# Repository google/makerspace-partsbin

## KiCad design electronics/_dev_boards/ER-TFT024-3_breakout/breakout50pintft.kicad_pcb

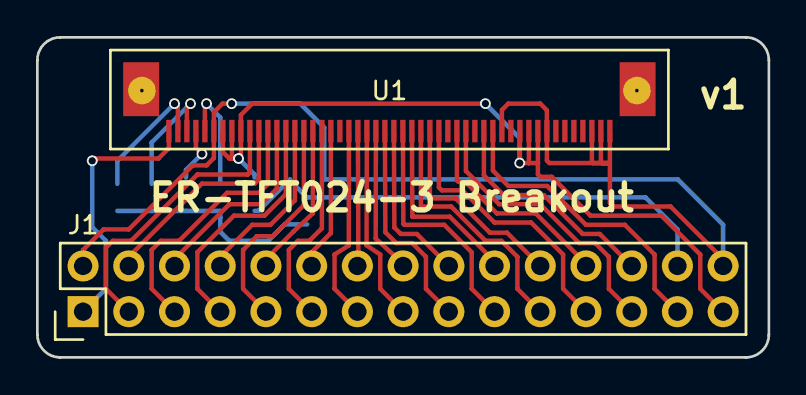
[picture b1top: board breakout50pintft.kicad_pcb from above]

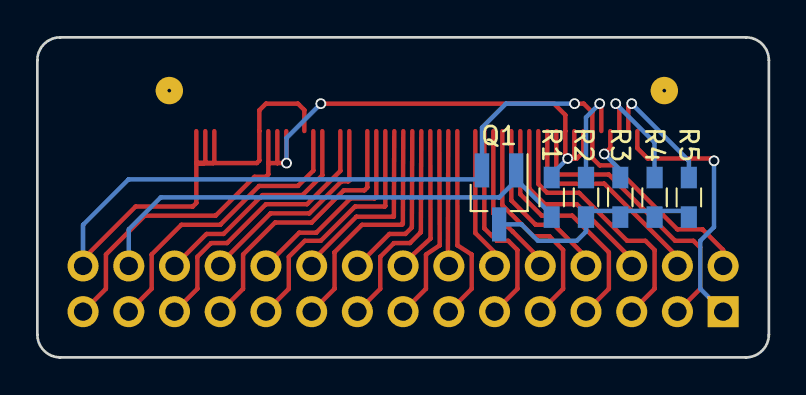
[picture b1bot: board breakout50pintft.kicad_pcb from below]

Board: 2 copper layers, 40.6 x 17.8 mm, 8 parts (6 on the bottom side), 34 nets.

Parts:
J1: CONN_02X15; Pin_Header_Straight_2x15
Q1: Q_PMOS_GSD; SOT-23_Handsoldering
R1: 10k; R_0603_HandSoldering
R2, R3, R4, R5: 330; R_0603_HandSoldering
U1: ER-TFT024-3; ZIF_50

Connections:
+3V3: J1.29, R1.2, U1.7, U1.8, U1.9, U1.40, U1.41, U1.42
+5V: J1.1, U1.1
BL: J1.28, Q1.1, R1.1
BLU3: J1.23, U1.31
BLU4: J1.22, U1.30
BLU5: J1.21, U1.29
BLU6: J1.20, U1.28
BLU7: J1.19, U1.27
CLOCK: J1.6, U1.13
DC: J1.26, U1.36
DEN: J1.7, U1.14
GND: J1.2, J1.30, Q1.2, U1.6, U1.38, U1.43, U1.48, U1.49, U1.50
GRE2: J1.18, U1.26
GRE3: J1.17, U1.25
GRE4: J1.16, U1.24
GRE5: J1.15, U1.23
GRE6: J1.14, U1.22
GRE7: J1.13, U1.21
HSYNC: J1.5, U1.12
MISO: J1.24, U1.33
MOSI: J1.25, U1.34
unnamed: Q1.3, R2.1, R3.1, R4.1, R5.1
unnamed: R2.2, U1.5
unnamed: R3.2, U1.4
unnamed: R4.2, U1.3
unnamed: R5.2, U1.2
RED3: J1.12, U1.19
RED4: J1.11, U1.18
RED5: J1.10, U1.17
RED6: J1.9, U1.16
RED7: J1.8, U1.15
RST: J1.3, U1.10
SCL: J1.27, U1.37
VSYNC: J1.4, U1.11

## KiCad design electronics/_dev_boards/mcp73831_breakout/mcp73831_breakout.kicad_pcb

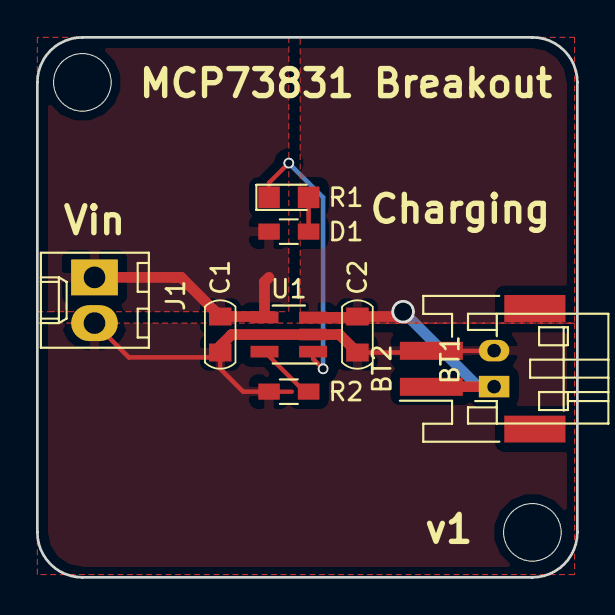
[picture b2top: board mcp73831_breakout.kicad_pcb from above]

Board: 2 copper layers, 30.0 x 30.0 mm, 10 parts (0 on the bottom side), 6 nets.

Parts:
BT1: Battery_Cell; JST_PH_S2B-PH-K_02x2.00mm_Angled
BT2: Battery_Cell; JST_PH_S2B-PH-SM4-TB_02x2.00mm_Angled
C1, C2: 4.7u; C_0805
D1: LED; LED_0805
J1: CONN_01X02; Molex_KK-6410-02_02x2.54mm_Straight
P1: SYMBOL; Board_Outline_30mm_Square
R1: 1k; R_0603_HandSoldering
R2: 2k; R_0603_HandSoldering
U1: MCP73831; SOT-23-5_HandSoldering

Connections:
/Vbat: BT1.1, BT2.1, C2.1, U1.3
/Vin: C1.1, J1.1, R1.2, U1.4
GND: BT1.2, BT2.2, C1.2, C2.2, J1.2, R2.2, U1.2
unnamed: D1.1, U1.1
unnamed: D1.2, R1.1
unnamed: R2.1, U1.5

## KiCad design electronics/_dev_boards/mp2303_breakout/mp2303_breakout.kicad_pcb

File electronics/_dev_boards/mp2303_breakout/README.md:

Not just for the 2303, also fits various newer MP devices such as MP2365.

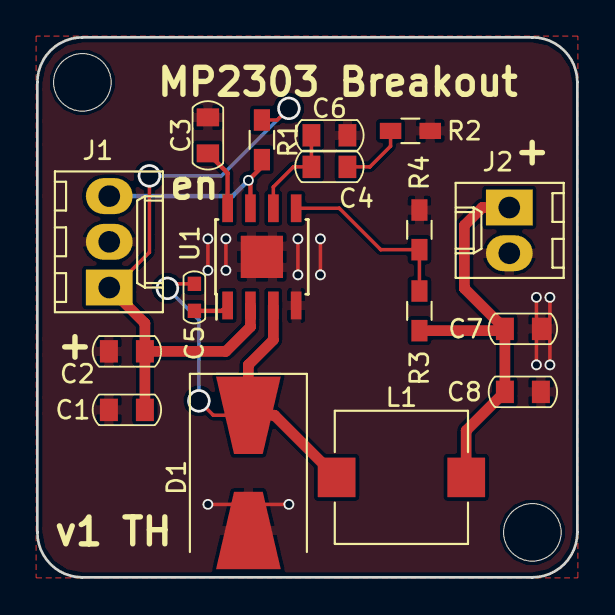
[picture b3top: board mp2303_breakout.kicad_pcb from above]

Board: 2 copper layers, 30.0 x 30.0 mm, 18 parts (0 on the bottom side), 10 nets.

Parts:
C1, C2: 10u; C_0805
C3: 0.1u; C_0805
C4: 3.3n; C_0805
C5: C; C_0603
C6: 50p; C_0805
C7, C8: 22u; C_0805
D1: D_Schottky; D_SMB-SMC_Universal_Handsoldering
J1: CONN_01X03; Molex_KK-6410-03_03x2.54mm_Straight
J2: CONN_01X02; Molex_KK-6410-02_02x2.54mm_Straight
L1: L; L_7.3x7.3_Handsoldering
P1: SYMBOL; Outline_30
R1, R2: 100k; R_0603_HandSoldering
R3: 52.5k; R_0603_HandSoldering
R4: 10k; R_0603_HandSoldering
U1: MP2303; SOIC-8-1EP_3.9x4.9mm_Pitch1.27mm

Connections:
/Vin: C1.1, C2.1, J1.1, R1.1, U1.2
/Vout: C7.1, C8.1, J2.1, L1.2, R3.1
/Vsw: C5.2, D1.1, L1.1, U1.3
GND: C1.2, C2.2, C3.2, C6.2, C7.2, C8.2, D1.2, J1.2, J2.2, R2.2, R4.2, U1.4, U1.9
unnamed: C3.1, U1.8
unnamed: C4.1, C6.1, U1.6
unnamed: C4.2, R2.1
unnamed: C5.1, U1.1
unnamed: J1.3, R1.2, U1.7
unnamed: R3.2, R4.1, U1.5

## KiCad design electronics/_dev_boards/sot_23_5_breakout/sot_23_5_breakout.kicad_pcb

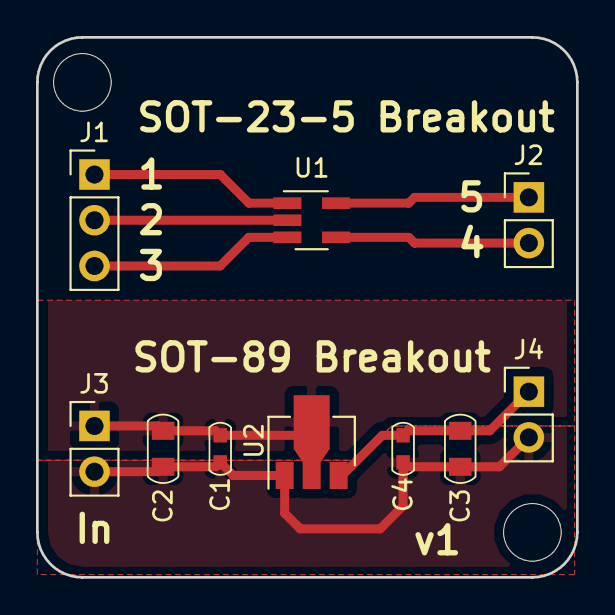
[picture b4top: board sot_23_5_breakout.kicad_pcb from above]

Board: 2 copper layers, 30.0 x 30.0 mm, 11 parts (0 on the bottom side), 8 nets.

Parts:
C1, C4: C; C_0603
C2, C3: C; C_0805
J1: CONN_01X03; Pin_Header_Straight_1x03_Pitch2.54mm
J2, J3, J4: CONN_01X02; Pin_Header_Straight_1x02_Pitch2.54mm
P1: SYMBOL; Board_Outline_30mm_Square
U1: SOT-23-5; SOT-23-5_HandSoldering
U2: MCP1703A-3302/MB; SOT89-3_Housing

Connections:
unnamed: C1.1, C2.1, J3.1, U2.2
unnamed: C1.2, C2.2, C3.2, C4.2, J3.2, J4.2, U2.1
unnamed: C3.1, C4.1, J4.1, U2.3
unnamed: J1.1, U1.1
unnamed: J1.2, U1.2
unnamed: J1.3, U1.3
unnamed: J2.1, U1.5
unnamed: J2.2, U1.4

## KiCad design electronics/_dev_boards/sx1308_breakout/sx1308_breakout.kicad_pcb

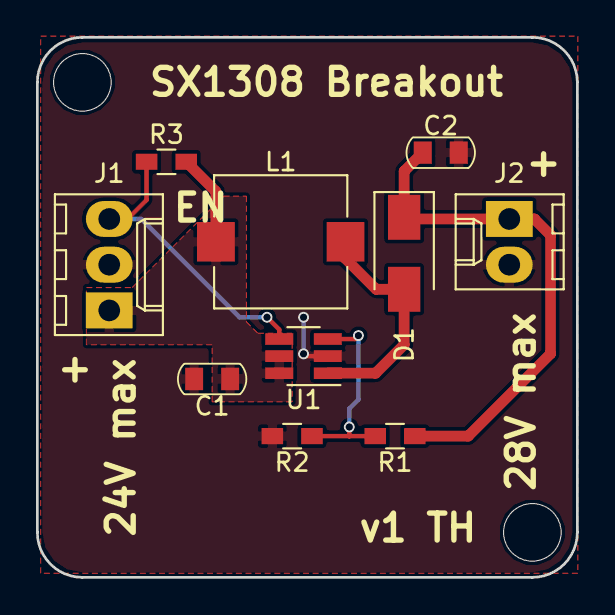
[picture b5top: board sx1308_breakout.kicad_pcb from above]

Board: 2 copper layers, 30.0 x 30.0 mm, 11 parts (0 on the bottom side), 6 nets.

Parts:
C1, C2: 22u; C_0805
D1: D_Schottky; D_SMA
J1: CONN_01X03; Molex_KK-6410-03_03x2.54mm_Straight
J2: CONN_01X02; Molex_KK-6410-02_02x2.54mm_Straight
L1: L; L_7.3x7.3_Handsoldering
P1: SYMBOL; Outline_30
R1, R2: R; R_0603_HandSoldering
R3: 100k; R_0603_HandSoldering
U1: SX1308; SOT-23-6_Handsoldering

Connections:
/Vin: C1.1, J1.1, L1.1, R3.1, U1.5, U1.6
/Vout: C2.1, D1.1, J2.1, R1.1
/Vsw: D1.2, L1.2, U1.1
GND: C1.2, C2.2, J1.2, J2.2, R2.2, U1.2
unnamed: J1.3, R3.2, U1.4
unnamed: R1.2, R2.1, U1.3

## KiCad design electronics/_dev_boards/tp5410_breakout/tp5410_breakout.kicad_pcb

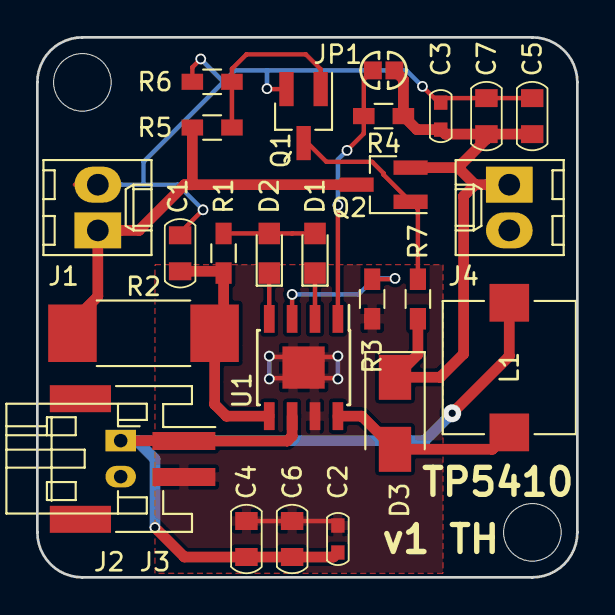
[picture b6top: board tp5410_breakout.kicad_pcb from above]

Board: 2 copper layers, 30.0 x 30.0 mm, 27 parts (0 on the bottom side), 13 nets.

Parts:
C1: 10u; C_0805
C2, C3: 0.1u; C_0603
C4, C5, C6, C7: 22u; C_0805
D1, D2: LED; LED_0805
D3: D; D_SMA
J1, J4: CONN_01X02; Molex_KK-6410-02_02x2.54mm_Straight
J2: CONN_01X02; JST_PH_S2B-PH-K_02x2.00mm_Angled
J3: CONN_01X02; JST_PH_S2B-PH-SM4-TB_02x2.00mm_Angled
JP1: Jumper_NO_Small; SJ_1_NO
L1: 4.7uH; L_7.3x7.3_Handsoldering
P1: 30mm; Outline_30
Q1: MMBT3904; SOT-23_Handsoldering
Q2: AO3401; SOT-23_Handsoldering
R1: R; R_0603_HandSoldering
R2: 0R3; R_2512_HandSoldering
R3: 680; R_0603_HandSoldering
R4: 293k; R_0603_HandSoldering
R5, R6: 5k; R_0603_HandSoldering
R7: 10k; R_0603_HandSoldering
U1: TP5410; SOIC-8-1EP_3.9x4.9mm_Pitch1.27mm

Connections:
/Vbat: C2.1, C4.1, C6.1, J2.1, J3.1, L1.2, U1.6
/Vchg: C1.1, R1.1, R2.2, U1.5
/Vin: J1.1, Q2.3, R2.1, R5.1
/Vout: C3.1, C5.1, C7.1, D3.1, J4.1, JP1.2, Q2.2, R4.2, R7.1
/Vsw: D3.2, L1.1, U1.8
GND: C1.2, C2.2, C3.2, C4.2, C5.2, C6.2, C7.2, J1.2, J2.2, J3.2, J4.2, Q1.2, R3.2, R6.2, U1.7, U1.9
unnamed: D1.1, U1.2
unnamed: D1.2, D2.2, R1.2
unnamed: D2.1, U1.4
unnamed: JP1.1, R4.1, U1.1
unnamed: Q1.1, R5.2, R6.1
unnamed: Q1.3, Q2.1, R7.2
unnamed: R3.1, U1.3

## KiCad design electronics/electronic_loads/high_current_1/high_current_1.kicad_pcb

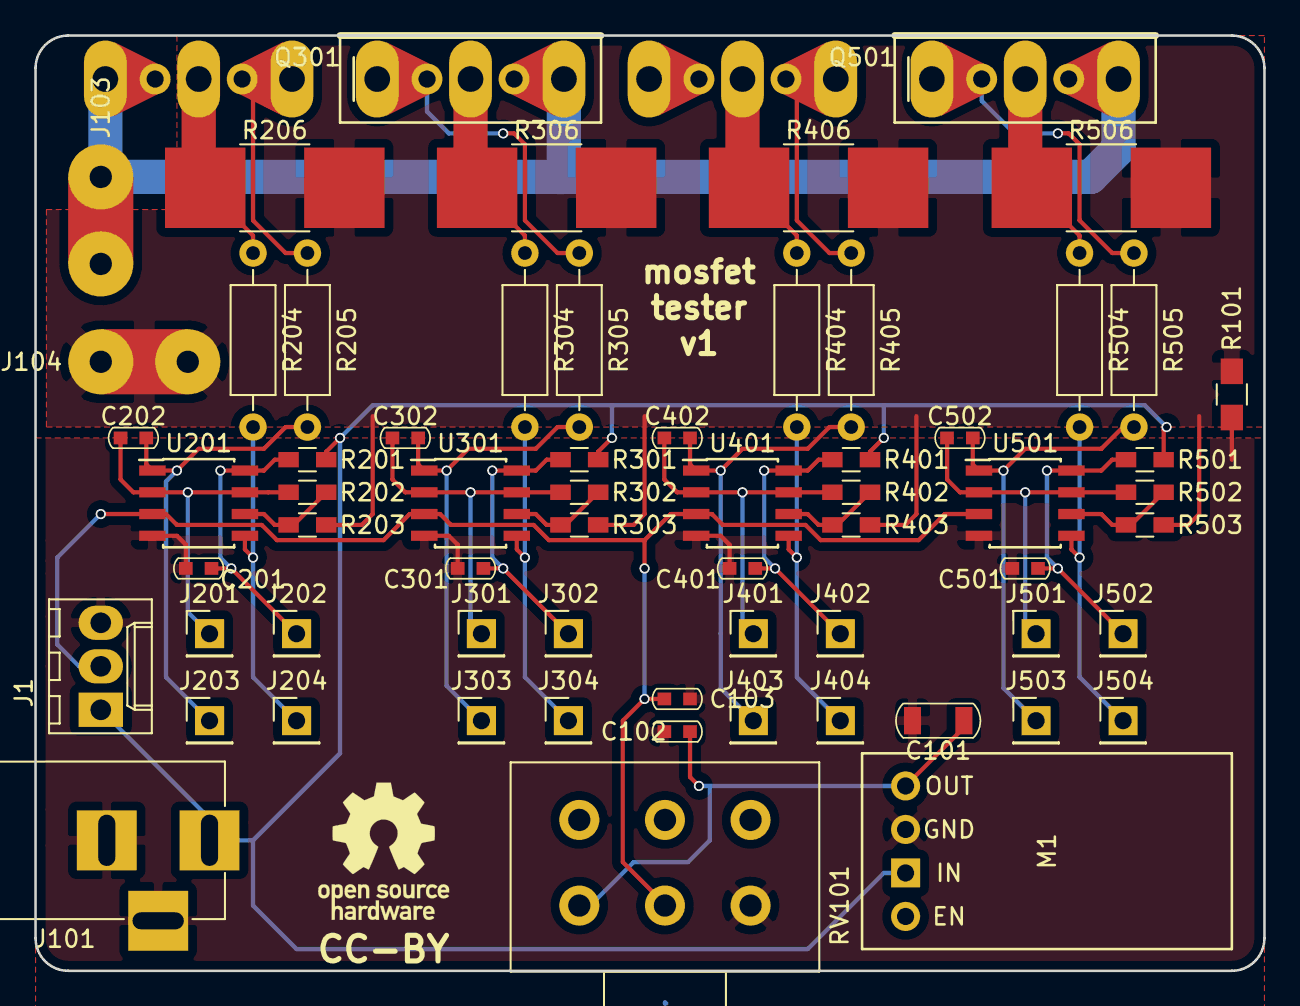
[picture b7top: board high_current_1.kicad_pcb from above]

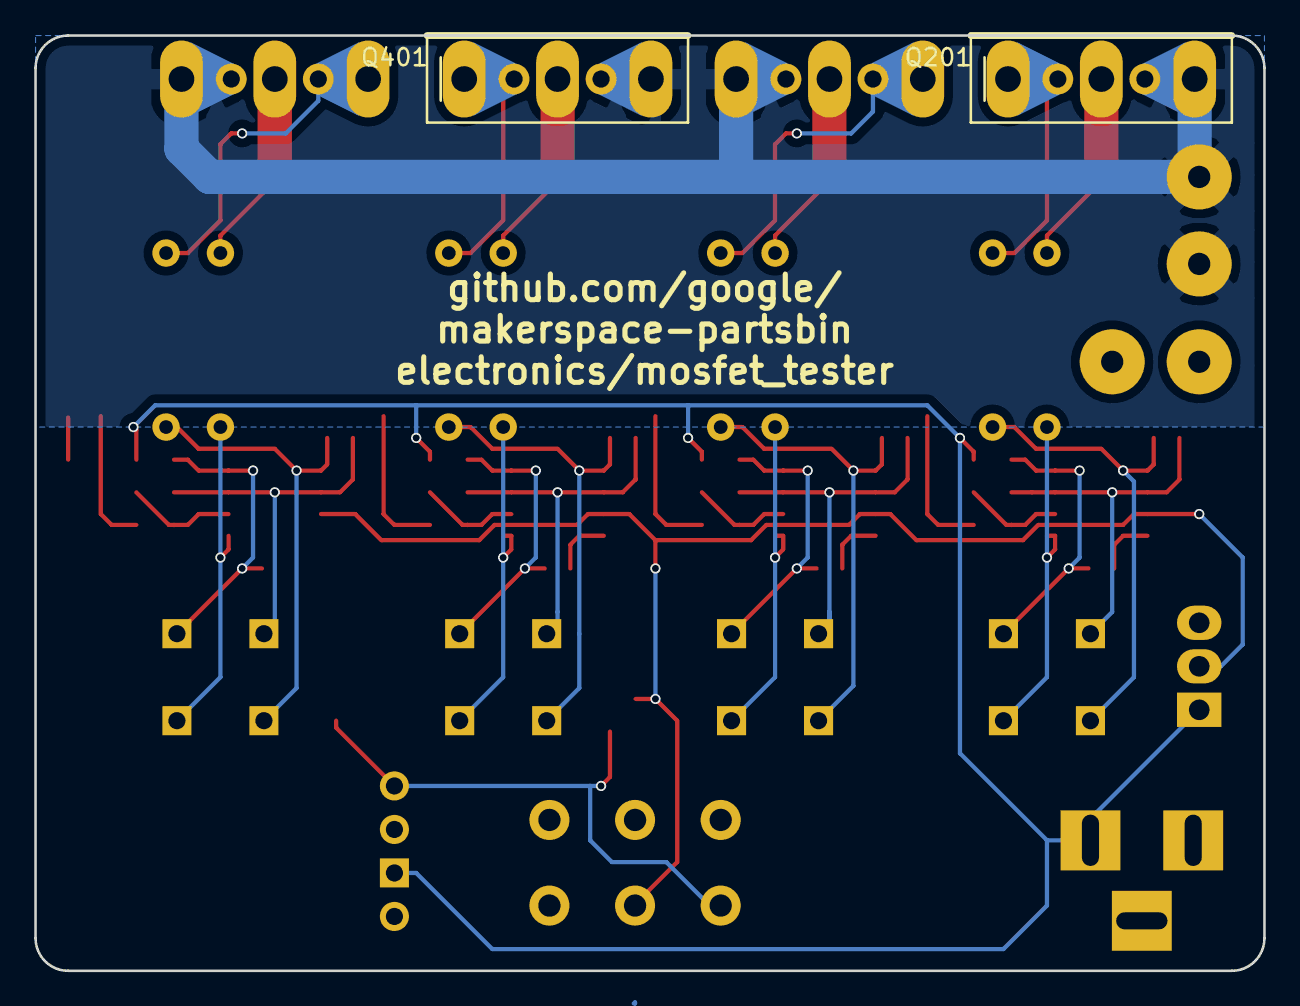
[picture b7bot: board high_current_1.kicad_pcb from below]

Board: 2 copper layers, 71.8 x 54.6 mm, 67 parts (2 on the bottom side), 34 nets.

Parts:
C101: 22u; C_1206
C102: 0.1u; C_0603
C103, C201, C301, C401, C501: 0.1; C_0603
C202, C302, C402, C502: C; C_0603
J1: CONN_01X03; Molex_KK-6410-03_03x2.54mm_Straight
J101: BARREL_JACK
J103, J104: Screw_Terminal_1x01; 2_Pin_Quick_Fit
J201, J202, J203, J204, J301, J302, J303, J304, J401, J402, J403, J404, J501, J502, J503, J504: TEST_1P; Pin_Header_Straight_1x01_Pitch2.54mm
M1: BuckModule; Buck_Module_7805_Replacement_Universal
P101: OSHW; OSHW-Logo_7.5x8mm_SilkScreen
Q201, Q301, Q401, Q501: Q_NMOS_GSD; TO_220_247
R101: 0R; R_0805_HandSoldering
R201, R301, R401, R501: 100R; R_0603_HandSoldering
R202, R203, R302, R303, R402, R403, R502, R503: R; R_0603_HandSoldering
R204, R205, R304, R305, R404, R405, R504, R505: R; R_Axial_DIN0207_L6.3mm_D2.5mm_P10.16mm_Horizontal
R206, R306, R406, R506: R; R_2816_HandSoldering
RV101: 10K; Potentiometer_Alps_RK163_Double_Vertical
U201, U301, U401, U501: LM358; SOIC-8_3.9x4.9mm_Pitch1.27mm

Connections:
+5V: C101.1, C102.1, M1.3, RV101.1
+12V: J1.1, J101.1, M1.1, R201.1, R301.1, R401.1, R501.1
/slice1/5V_REF: C103.1, J1.2, RV101.2, U201.3, U301.3, U401.3, U501.3
/slice1/VIN+: J103.1, Q201.3, Q301.3, Q401.3, Q501.3
/slice1/VIN-: J104.1, R101.1, R203.1, R206.2, R303.1, R306.2, R403.1, R406.2, R503.1, R506.2
/slice1/Vgs: C202.1, J203.1, R205.2, U201.1
/slice2/Vgs: C302.1, J303.1, R305.2, U301.1
/slice3/Vgs: C402.1, J403.1, R405.2, U401.1
/slice4/Vgs: C502.1, J503.1, R505.2, U501.1
GND: C101.2, C102.2, C103.2, C201.1, C301.1, C401.1, C501.1, J1.3, J101.2, J101.3, M1.2, R101.2, RV101.3, U201.4, U301.4, U401.4, U501.4
unnamed: C201.2, J202.1, R201.2, U201.8
unnamed: C202.2, J201.1, R202.2, U201.2, U201.7
unnamed: C301.2, J302.1, R301.2, U301.8
unnamed: C302.2, J301.1, R302.2, U301.2, U301.7
unnamed: C401.2, J402.1, R401.2, U401.8
unnamed: C402.2, J401.1, R402.2, U401.2, U401.7
unnamed: C501.2, J502.1, R501.2, U501.8
unnamed: C502.2, J501.1, R502.2, U501.2, U501.7
unnamed: J204.1, R204.2, U201.5
unnamed: J304.1, R304.2, U301.5
unnamed: J404.1, R404.2, U401.5
unnamed: J504.1, R504.2, U501.5
unnamed: Q201.1, R205.1
unnamed: Q201.2, R204.1, R206.1
unnamed: Q301.1, R305.1
unnamed: Q301.2, R304.1, R306.1
unnamed: Q401.1, R405.1
unnamed: Q401.2, R404.1, R406.1
unnamed: Q501.1, R505.1
unnamed: Q501.2, R504.1, R506.1
unnamed: R202.1, R203.2, U201.6
unnamed: R302.1, R303.2, U301.6
unnamed: R402.1, R403.2, U401.6
unnamed: R502.1, R503.2, U501.6

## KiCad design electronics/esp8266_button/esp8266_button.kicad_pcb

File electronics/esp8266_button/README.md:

# Basic use

Assemble board.  The board itself is 40x50mm, and the mounting holes (centered)
are 32x42mm.  You probably want a 3d printed housing for it, but you need to
choose whether it's powered all the time (using deep sleep), or fully powers off
unless you tap SW1.  (Close one of "DSleep" or "Button" solder jumpers.)

Keep GPIO12 set HIGH to power things (including the battery monitor ADC pin and
the BMP180 header), otherwise set LOW to conserve power.

Shields based on the Wemos D1 Mini pinout should fit (though collide with SW1),
and will also be depowered by GPIO12.

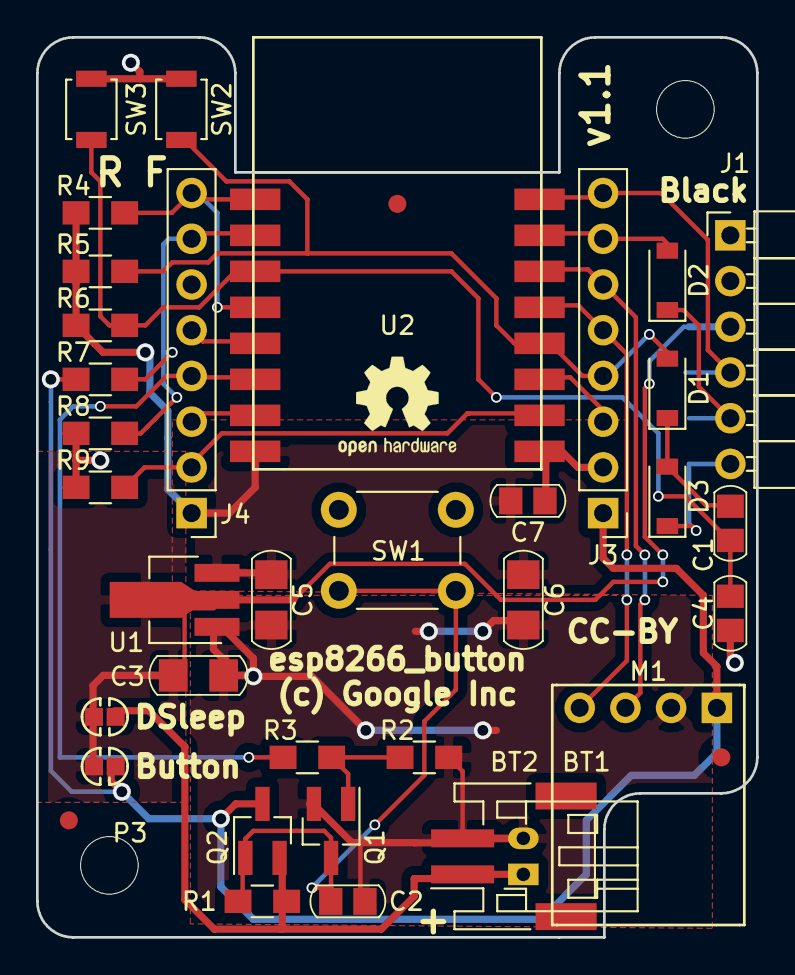
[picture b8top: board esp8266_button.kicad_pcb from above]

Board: 2 copper layers, 40.0 x 50.0 mm, 41 parts (1 on the bottom side), 23 nets.

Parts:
BT1: Battery_Cell; JST_PH_S2B-PH-K_02x2.00mm_Angled
BT2: Battery_Cell; JST_PH_S2B-PH-SM4-TB_02x2.00mm_Angled
C1, C2, C4, C7: 220p; C_0805
C3, C5, C6: 10u; C_1206
D1, D2, D3: B5819W; D_SOD-123
J1: CONN_01X06; Pin_Header_Angled_1x06_Pitch2.54mm
J2: CONN_01X06; Pogo_6
J3, J4: CONN_01X08; Pin_Header_Straight_1x08_Pitch2.54mm
JP1: Always On; SJ_1_NO
JP2: MOS Control; SJ_1_NO
M1: BMP180_Breakout; BMxx80
P1, P2, P3: Fid; Fiducial_1mm_Dia_2.54mm_Outer_CopperTop
P4: OSHW; OSHW-Logo2_7.3x6mm_SilkScreen
P5, P6: M3 Hole; MountingHole_3.2mm_M3
Q1: Q_NMOS_GSD; SOT-23_Handsoldering
Q2: Q_PMOS_GSD; SOT-23_Handsoldering
R1, R8: 100k; R_0805_HandSoldering
R2: 220k; R_0805_HandSoldering
R3, R4, R5, R6, R9: 10k; R_0805_HandSoldering
R7: 320k; R_0805_HandSoldering
SW1: SW_Push; SW_PUSH_6mm
SW2, SW3: SW_Push; SW_SPST_B3U-1000P
U1: MCP1703A-3302/MB; SOT-89-3_Handsoldering
U2: ESP-12; ESP-12E

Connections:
+3V3: C5.1, C6.1, C7.1, J4.1, R4.2, R5.2, R6.2, U1.3, U2.8
/ADC: J4.7, R7.2, R8.1, U2.2
/GPIO2: J3.3, U2.11
/GPIO4: J3.5, M1.4, U2.13
/GPIO5: J3.6, M1.3, U2.14
/GPIO13: J4.3, U2.7
/GPIO14: J4.5, U2.5
/GPIO15: J4.2, R9.2, U2.10
/Vbat: BT1.1, BT2.1, JP1.1, Q2.2, R1.1
BATTMON: J3.1, JP2.1, M1.1, Q2.3, R7.1
CH_PD: C1.2, C4.2, R6.1, SW3.2, U2.3
GND: BT1.2, BT2.2, C2.2, C3.2, C4.1, C5.2, C6.2, C7.2, J1.1, J2.1, J3.2, M1.2, Q1.2, R2.2, R8.2, R9.1, SW1.1, SW2.1, SW3.1, U1.1, U2.9
GPIO0: D1.2, J3.4, R5.1, SW2.2, U2.12
GPIO12: J4.4, R3.1, U2.6
unnamed: C1.1, D1.1, D3.2
unnamed: D2.1, J1.5, J2.5
unnamed: D3.1, J1.6, J2.6
unnamed: Q1.1, R2.1, R3.2
PWRIN: C3.1, J1.3, J2.3, JP1.2, JP2.2, U1.2
RESET: J4.8, R4.1, U2.1, U2.4
RXD: D2.2, J3.7, U2.15
TXD: J1.4, J2.4, J3.8, U2.16
~POWERON: C2.1, Q1.3, Q2.1, R1.2, SW1.2

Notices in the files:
electronics/electronic_loads/high_current_1/high_current_1.kicad_pcb:
CC-BY
